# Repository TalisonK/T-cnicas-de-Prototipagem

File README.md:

# Tecnicas-de-Prototipagem
repositório destinado a agrupar as atividades da disciplina de Técnicas de Prototipagem.

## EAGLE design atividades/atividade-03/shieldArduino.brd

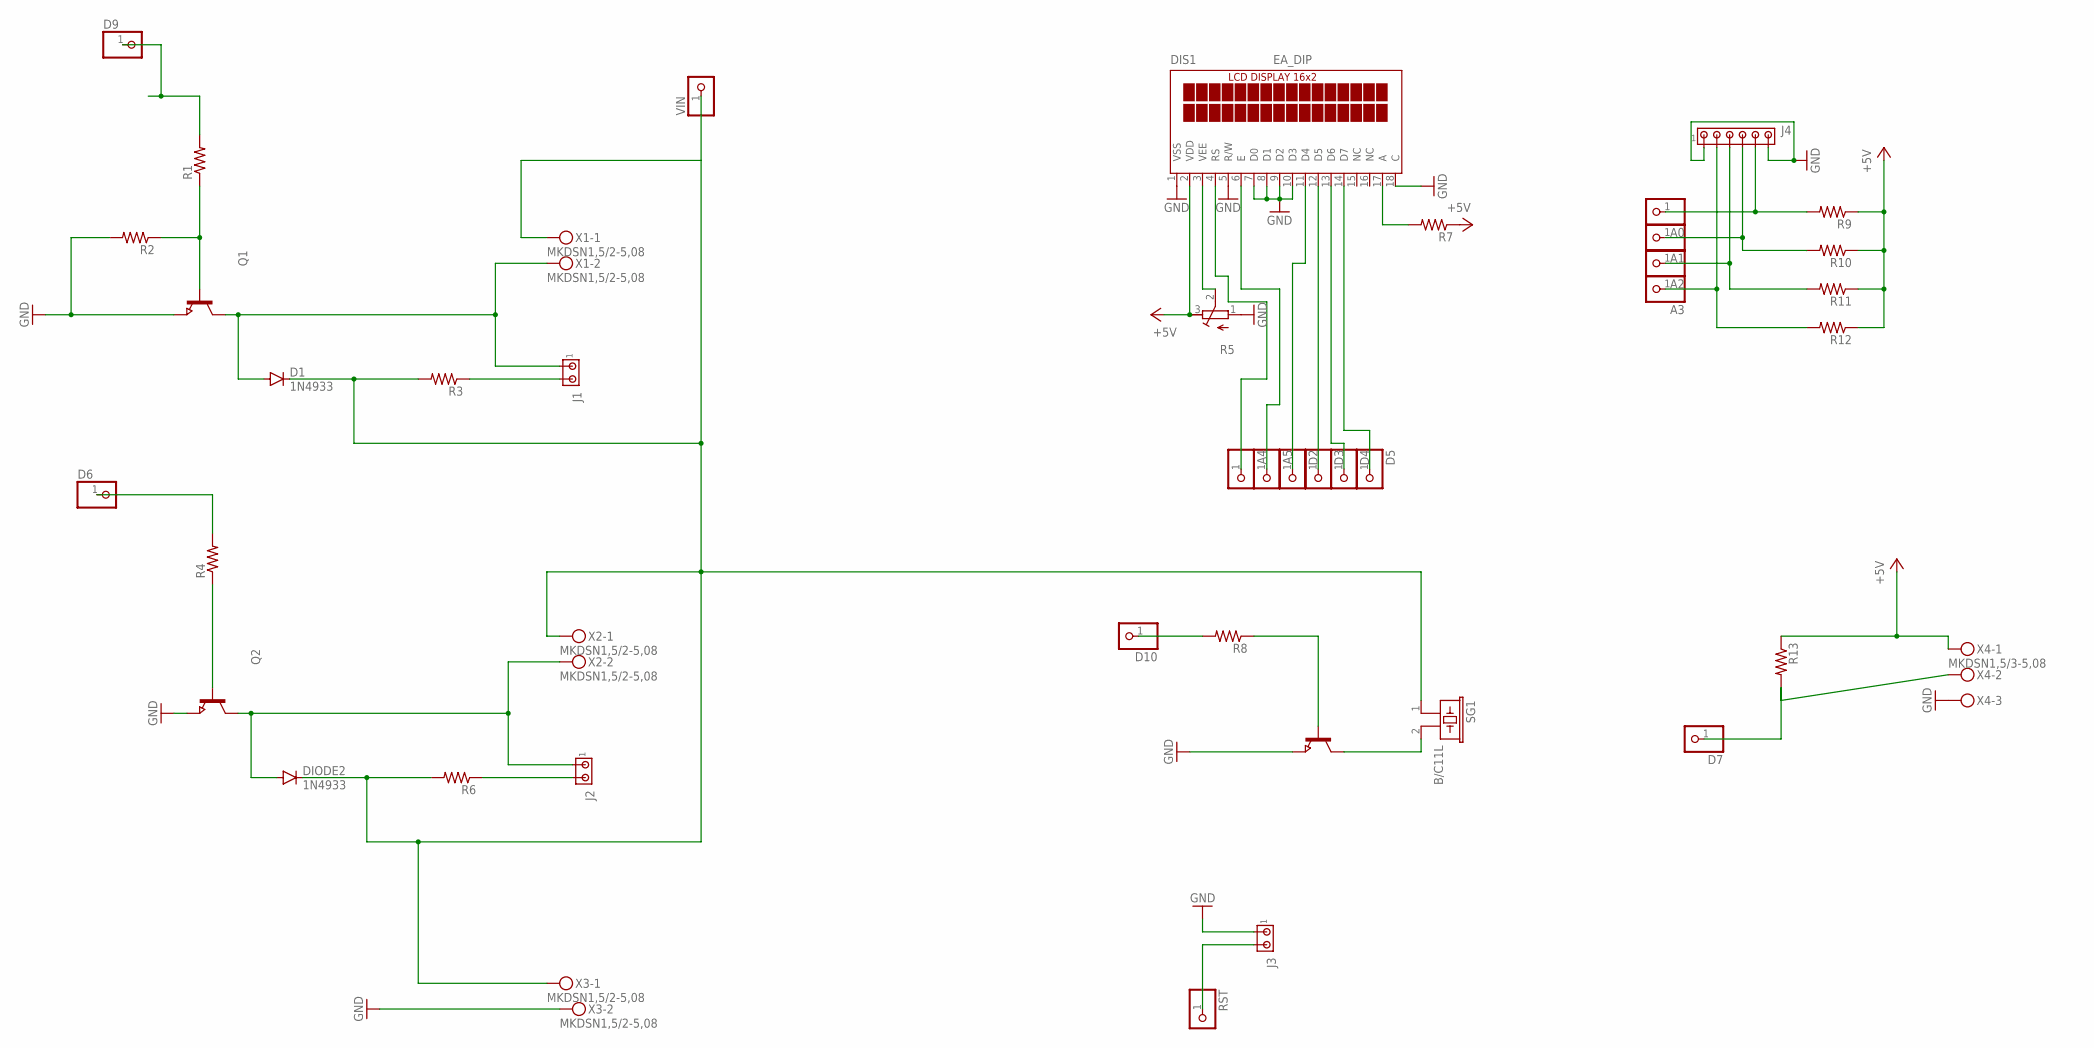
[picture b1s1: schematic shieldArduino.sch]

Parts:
A0, A1, A2, A3, A4, A5: PINHD-1X1; 1X01
D1: 1N4933; DO41-10
D2, D3, D4, D5, D6, D7, D9, D10: PINHD-1X1; 1X01
DIODE2: 1N4933; DO41-10
DIS1: EA_DIP
J1, J2, J3: MTA02-156; 1X2MTA
J4: MTA06-156; 1X6MTA
Q1, Q2, Q3: NPN-TRANSISTOR_SOT23W; SOT23W
R1, R2, R3, R4, R6, R7, R8, R9, R10, R11, R12, R13: R-US_0617/22; 0617/22
R5: R-TRIMM3339P; RTRIM3339P
RST: PINHD-1X1; 1X01
SG1: B/C11L
VIN: PINHD-1X1; 1X01
X1, X2, X3: MKDSN1,5/2-5,08
X4: MKDSN1,5/3-5,08

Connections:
+5V: DIS1.2 (VDD), R5.3 (E), R7.1, R9.1, R10.1, R11.1, R12.1, R13.1, X4.1
A4: A4.1, DIS1.4 (RS)
D6: D6.1, R4.2
GND: DIS1.1 (VSS), DIS1.5 (R/W), DIS1.7 (D0), DIS1.8 (D1), DIS1.9 (D2), DIS1.10 (D3), DIS1.18 (C), J3.1, J4.1, J4.6, Q1.3 (E), Q2.3 (E), Q3.3 (E), R2.2, R5.1 (A), X3.2, X4.3
unnamed: Q1.1 (B), R1.1, R2.1
unnamed: D1.A, J1.1, Q1.2 (C), X1.2
unnamed: J1.2, R3.1
unnamed: D9.1, R1.2
unnamed: Q2.1 (B), R4.1
unnamed: DIODE2.A, J2.1, Q2.2 (C), X2.2
unnamed: J2.2, R6.1
unnamed: A5.1, DIS1.6 (E)
unnamed: D2.1, DIS1.11 (D4)
unnamed: DIS1.3 (VEE), R5.2 (S)
unnamed: D3.1, DIS1.12 (D5)
unnamed: D4.1, DIS1.13 (D6)
unnamed: D5.1, DIS1.14 (D7)
unnamed: DIS1.17 (A), R7.2
unnamed: Q3.1 (B), R8.1
unnamed: D10.1, R8.2
unnamed: Q3.2 (C), SG1.2
unnamed: J3.2, RST.1
unnamed: A0.1, J4.5, R9.2
unnamed: A1.1, J4.4, R10.2
unnamed: A2.1, J4.3, R11.2
unnamed: A3.1, J4.2, R12.2
unnamed: D7.1, R13.2, X4.2
VIN: D1.C, DIODE2.C, R3.2, R6.2, SG1.1, VIN.1, X1.1, X2.1, X3.1

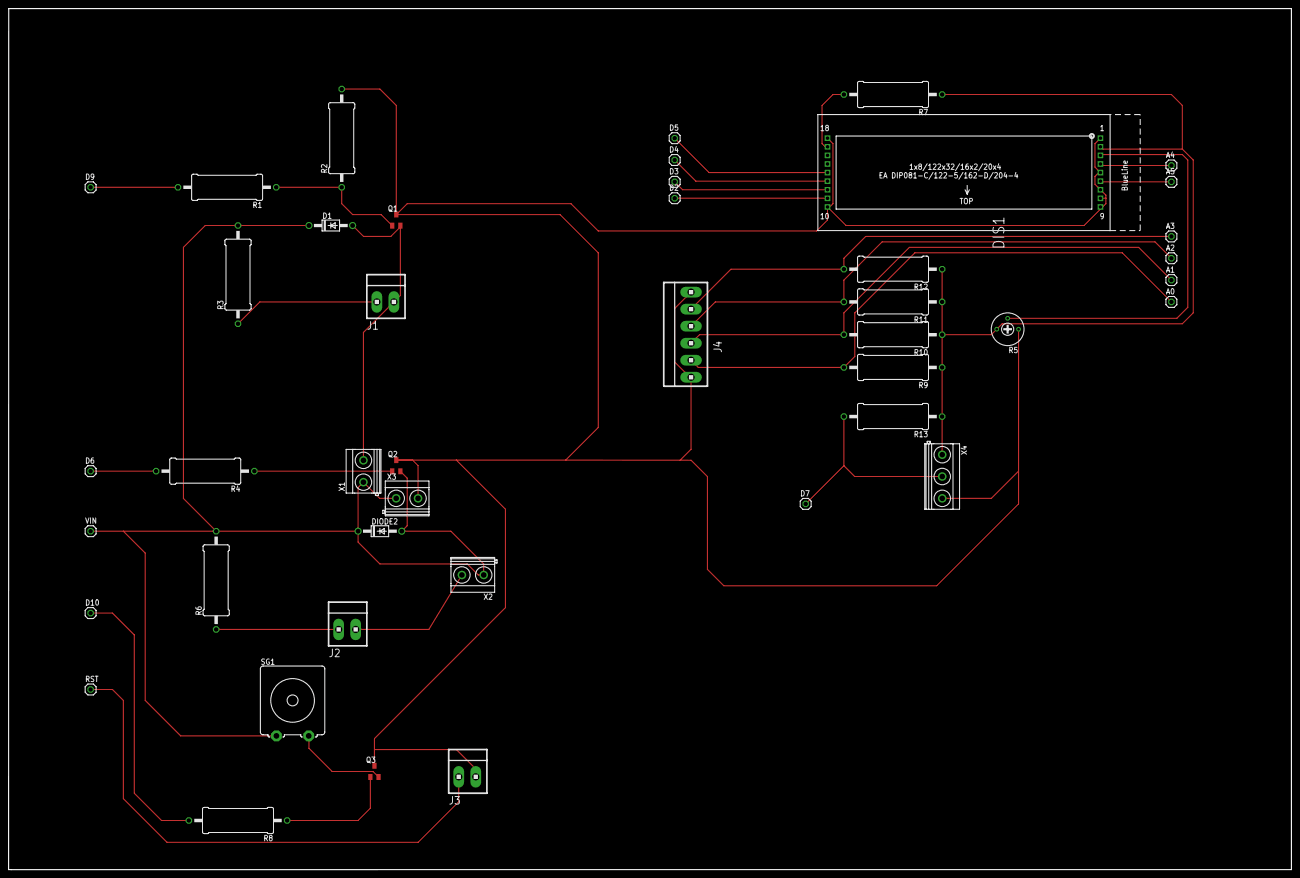
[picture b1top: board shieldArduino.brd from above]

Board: 2 copper layers, 298.5 x 200.3 mm, 44 parts (0 on the bottom side), 28 nets.

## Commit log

2021-12-04 atividade 2
2021-12-04 adição da atividade 2
2021-12-04 correção
2021-12-20 adição da atividade 3
2021-12-29 adição da atividade 4
